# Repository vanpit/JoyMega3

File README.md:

# JoyMega3
 JoyMega3 MD to MSX adapter

C1 - 100nF

D1, D2 - 1N5711

IC1 - NC7ST04M5X

Connectors - ENCITECH DM09-SP, DM09-SS

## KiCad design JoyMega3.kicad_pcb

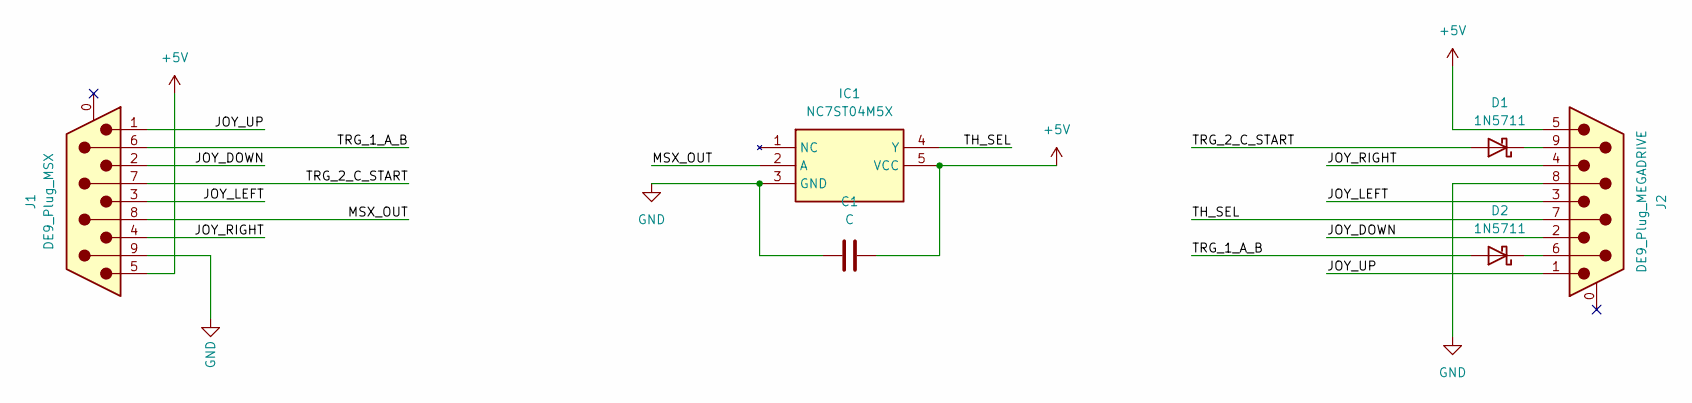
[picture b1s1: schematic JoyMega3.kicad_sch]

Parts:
C1: C; C_Disc_D7.5mm_W2.5mm_P5.00mm
D1, D2: 1N5711; D_DO-35_SOD27_P7.62mm_Horizontal
IC1: NC7ST04M5X; SOT-23-5_HandSoldering; Manufacturer_Part_Number NC7ST04M5X
J1: DE9_Plug_MSX; DSUB-9_Female_EdgeMount_P2.77mm
J2: DE9_Plug_MEGADRIVE; DSUB-9_Male_Horizontal_P2.77x2.84mm_EdgePinOffset4.94mm_Hou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

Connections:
+5V: C1.1, IC1.5 (VCC), J1.5, J2.5
/JOY_DOWN: J1.2, J2.2
/JOY_LEFT: J1.3, J2.3
/JOY_RIGHT: J1.4, J2.4
/JOY_UP: J1.1, J2.1
/MSX_OUT: IC1.2 (A), J1.8
/TH_SEL: IC1.4 (Y), J2.7
/TRG_1_A_B: D2.2 (A), J1.6
/TRG_2_C_START: D1.2 (A), J1.7
GND: C1.2, IC1.3 (GND), J1.9, J2.8
unnamed: D1.1 (K), J2.9
unnamed: D2.1 (K), J2.6

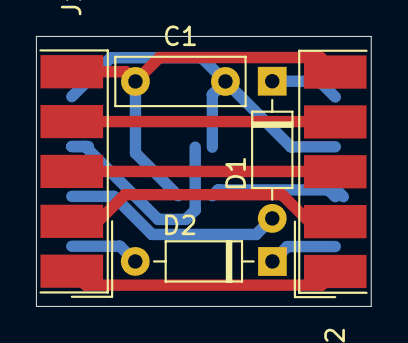
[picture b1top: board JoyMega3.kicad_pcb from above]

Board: 2 copper layers, 18.6 x 15.0 mm, 6 parts (1 on the bottom side), 12 nets.

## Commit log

2024-03-31 Added more pictures
2024-04-01 Added elements specification
